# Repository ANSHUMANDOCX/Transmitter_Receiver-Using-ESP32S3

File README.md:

# Transmitter_Receiver-Using-ESP32S3
This is an RF ESP32-S3-based 10-channel Transmitter and Receiver which can also be used with the ESP-NOW protocol.

## PARTS
- ESP32-S3 WROOM-1U
- NRF24L01+ Transceiver Module
- SSD1309 2.42 inch OLED
- 2 Joysticks
- 4 Switches
- 2 Potentiometers

## PLAN
This is an RF transmitter with 10 channels, all of which support PWM output. The 10 channels include: 4 from joysticks 2 from potentiometers 4 from toggle switches

The setup includes a 2.42-inch OLED display to show the status of each channel, bind status, and battery level.

The receiver and transmitter will be programmed using an FTDI module.

The transmitter is designed to run for 5–6 hours on a 1000mAh LiPo battery (ideally).

The code is subject to change depending on in hand testing currently its just a sample code for controlling 10 servo motor with the 10 inputs.
# Transmitter 

# Receiver

## BOM

| Supplier             | Item                                           | Price (USD) |
|----------------------|------------------------------------------------|-------------|
| **LCSC**             | Joystick (x2)                                  | $0.85       |
|                      | SSD1309 2.42" OLED                             | $11.28      |
|                      | ESP32-S3 WROOM                                 | $7.69       |
|                      | Potentiometer (x2)                             | $3.31       |
|                      | Switches (x4)                                  | $2.33       |
|                      | MIC5219 3.3V LDO                               | $1.41       |
|                      | Pin headers+passive component                  | $7.71       |
|                      | Shipping                                       | $3.74       |
|                      | **Total (LCSC)**                               | **$38.05**  |
| **JLCPCB**           | PCB                                            | $6.00       |
|                      | Shipping                                       | $14.00      |
|                      | **Total (JLCPCB)**                             | **$20.00**  |
| **Sharvi Electronics** | nRF24L01+ + Heatset Insert + Charging Module+antenna | $9.53|
|                      | **Total (Sharvi)**                             | **$9.53**   |
| **Electronics Comp.** | Battery                                        | $5.38       |
|                      | **Total (Electronics Comp.)**                 | **$5.38**   |

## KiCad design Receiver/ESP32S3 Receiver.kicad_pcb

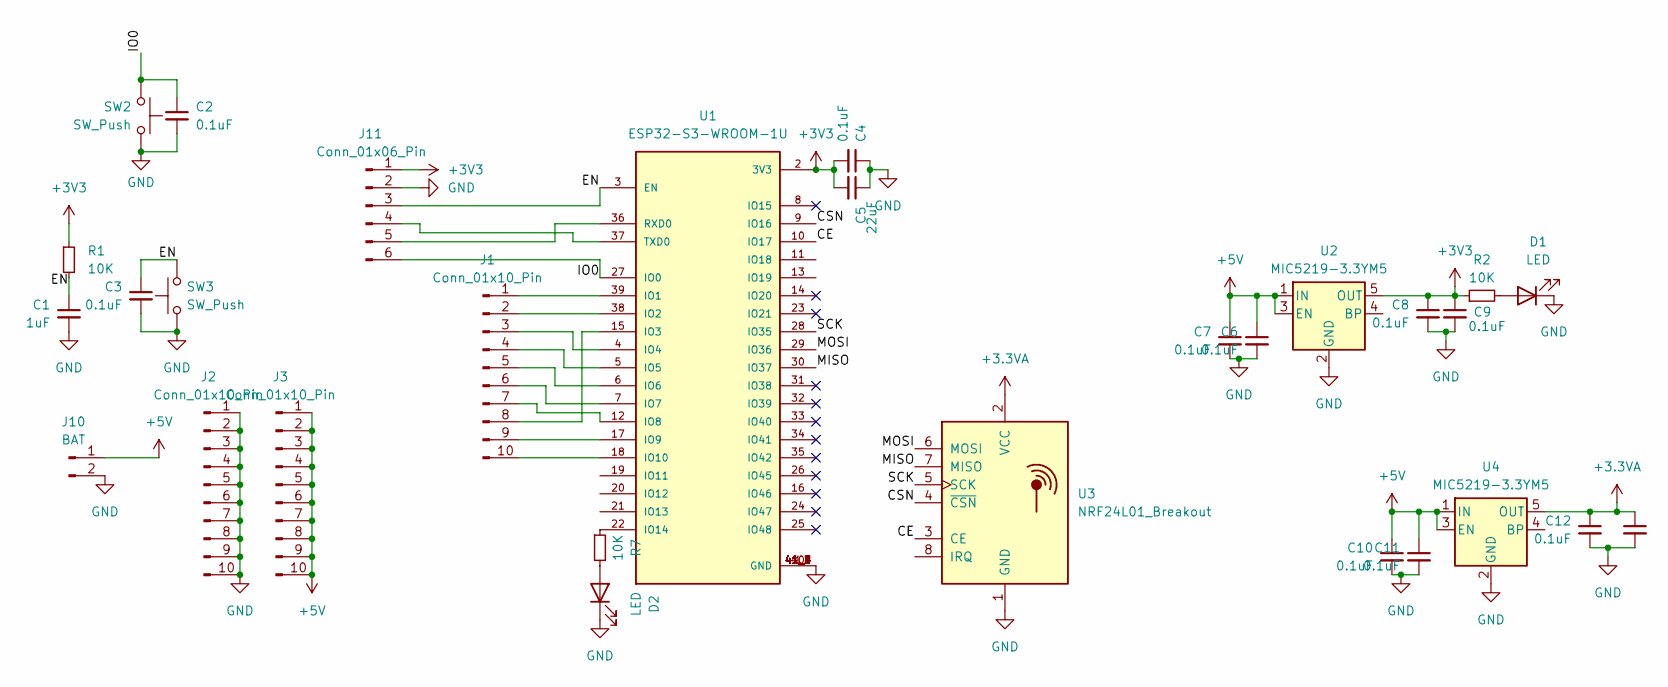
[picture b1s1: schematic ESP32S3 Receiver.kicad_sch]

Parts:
C1: 1uF; C_0603_1608Metric
C2, C3, C4, C6, C7, C8, C9, C10, C11, C12, C13: 0.1uF; C_0603_1608Metric
C5: 22uF; C_0603_1608Metric
D1, D2: LED; LED_0603_1608Metric_Pad1.05x0.95mm_HandSolder
J1, J2, J3: Conn_01x10_Pin; PinHeader_1x10_P2.54mm_Vertical
J10: BAT; PinHeader_1x02_P1.27mm_Vertical
J11: Conn_01x06_Pin; PinHeader_1x06_P1.27mm_Vertical
R1, R2, R7: 10K; R_0603_1608Metric
SW2, SW3: SW_Push; SW_Push_SPST_NO_Alps_SKRK
U1: ESP32-S3-WROOM-1U; XCVR_ESP32-S3-WROOM-1U; PARTREV v0.6
U2, U4: MIC5219-3.3YM5; SOT-23-5
U3: NRF24L01_Breakout; nRF24L01_Breakout

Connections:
+3.3VA: C12.1, C13.1, U3.2 (VCC), U4.5 (OUT)
+3V3: C4.2, C5.2, C8.1, C9.1, J11.1, R1.1, R2.1, U1.2 (3V3), U2.5 (OUT)
+5V: C6.1, C7.1, C10.1, C11.1, J3.1, J3.2, J3.3, J3.4, J3.5, J3.6, J3.7, J3.8, J3.9, J3.10, J10.1, U2.1 (IN), U2.3 (EN), U4.1 (IN), U4.3 (EN)
/CE: U1.10 (IO17), U3.3 (CE)
/CSN: U1.9 (IO16), U3.4 (~CSN)
/EN: C1.1, C3.1, J11.3, R1.2, SW3.2, U1.3 (EN)
/IO0: C2.1, J11.6, SW2.2, U1.27 (IO0)
/MISO: U1.30 (IO37), U3.7 (MISO)
/MOSI: U1.29 (IO36), U3.6 (MOSI)
/SCK: U1.28 (IO35), U3.5 (SCK)
GND: C1.2, C2.2, C3.2, C4.1, C5.1, C6.2, C7.2, C8.2, C9.2, C10.2, C11.2, C12.2, C13.2, D1.1 (K), D2.1 (K), J2.1, J2.2, J2.3, J2.4, J2.5, J2.6, J2.7, J2.8, J2.9, J2.10, J10.2, J11.2, SW2.1, SW3.1, U1.1 (GND), U1.40 (GND), U1.41_1 (GND), U1.41_2 (GND), U1.41_3 (GND), U1.41_4 (GND), U1.41_5 (GND), U1.41_6 (GND), U1.41_7 (GND), U1.41_8 (GND), U1.41_9 (GND), U2.2 (GND), U3.1 (GND), U4.2 (GND)
unnamed: D1.2 (A), R2.2
unnamed: D2.2 (A), R7.2
unnamed: J1.1, U1.39 (IO1)
unnamed: J1.2, U1.38 (IO2)
unnamed: J1.3, U1.4 (IO4)
unnamed: J1.4, U1.5 (IO5)
unnamed: J1.5, U1.6 (IO6)
unnamed: J1.6, U1.7 (IO7)
unnamed: J1.7, U1.12 (IO8)
unnamed: J1.8, U1.15 (IO3)
unnamed: J1.9, U1.17 (IO9)
unnamed: J1.10, U1.18 (IO10)
unnamed: J11.4, U1.37 (TXD0)
unnamed: J11.5, U1.36 (RXD0)
unnamed: R7.1, U1.22 (IO14)

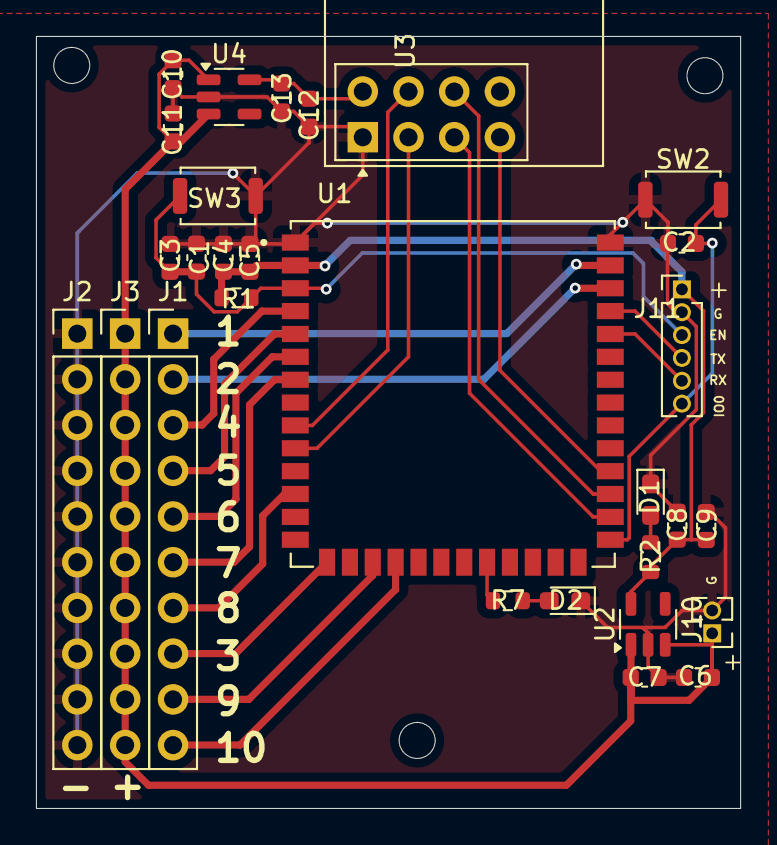
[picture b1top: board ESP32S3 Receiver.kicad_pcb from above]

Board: 2 copper layers, 39.1 x 42.9 mm, 29 parts (0 on the bottom side), 26 nets.

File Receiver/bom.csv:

Designator,Footprint,Quantity,Value,LCSC Part #
C1,0603,1,1uF,
"C10, C11, C12, C13, C2, C3, C4, C6, C7, C8, C9",0603,11,0.1uF,
C5,0603,1,22uF,
"D1, D2",0603,2,LED,
"J1, J2, J3",PinHeader_1x10_P2.54mm_Vertical,3,Conn_01x10_Pin,
J10,PinHeader_1x02_P1.27mm_Vertical,1,BAT,
J11,PinHeader_1x06_P1.27mm_Vertical,1,Conn_01x06_Pin,
"R1, R2, R7",0603,3,10K,
"SW2, SW3",SW_Push_SPST_NO_Alps_SKRK,2,SW_Push,
U1,XCVR_ESP32-S3-WROOM-1U,1,ESP32-S3-WROOM-1U,
"U2, U4",SOT-23-5,2,MIC5219-3.3YM5,
U3,nRF24L01_Breakout,1,NRF24L01_Breakout,

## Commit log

2025-06-30 Create CAD
2025-06-30 Create fg
2025-06-30 Create s
